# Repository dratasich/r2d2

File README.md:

# r2d2
Software, 3D drawings for R2D2 build.

## Contents

* `firmware_uc_body` contains the sources for the ATmega2560 microcontroller
  (Arduino Mega) controlling body parts (e.g., dome motor).

* `cad` contains FreeCAD projects for R2D2 (e.g., custom dome bearing).

* `pcb` holds Kicad projects for PCBs used in R2D2 (e.g., motor driver shield).

## Dependencies

For some cad drawings the library
[JohK/nutsnbolts](https://github.com/JohK/nutsnbolts) is used.

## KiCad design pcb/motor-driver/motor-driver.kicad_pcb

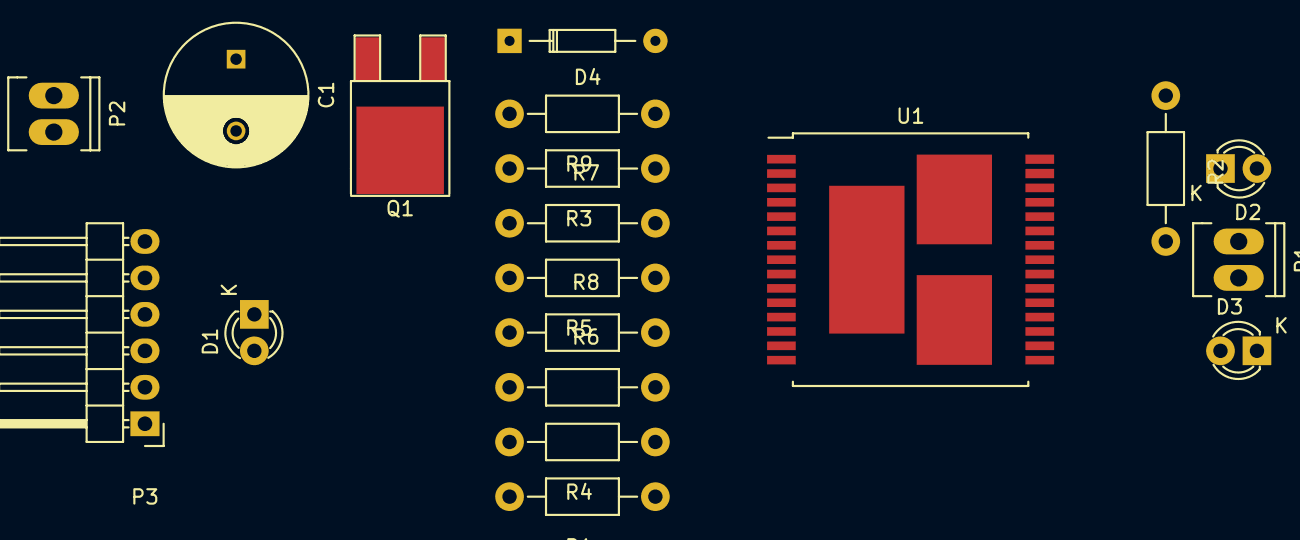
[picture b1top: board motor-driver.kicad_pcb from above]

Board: 2 copper layers, 19 parts (0 on the bottom side), 18 nets, no tracks yet.

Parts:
C1: 1u; C_Radial_D10_L20_P5
D1, D2, D3: LED; LED-3MM
D4: ZENER; Diode_DO-35_SOD27_Horizontal_RM10
P1, P2: CONN_01X02; Socket_MOLEX-KK-RM2-54mm_Lock_2pin_straight
P3: CONN_01X06; Pin_Header_Angled_1x06
Q1: IRF540N; TO-252-2Lead
R1: 330R; Resistor_Horizontal_RM10mm
R2: 120R; Resistor_Horizontal_RM10mm
R3, R4, R5: 1k; Resistor_Horizontal_RM10mm
R6, R7: 3k3; Resistor_Horizontal_RM10mm
R8: 1k5; Resistor_Horizontal_RM10mm
R9: 100k; Resistor_Horizontal_RM10mm
U1: VNH2SP30-E; MultiPowerSO-30_16x17.2mm_Pitch1mm

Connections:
+5V: P3.1, R1.1, R6.1, R7.1
/CS: P3.5, R8.2, U1.9
/INA: P3.3, R3.2
/INB: P3.4, R4.2
/OUTA: P1.1, R2.2, U1.1, U1.25, U1.30
/OUTB: D2.1, D3.2, P1.2, U1.15, U1.16, U1.21
/PWM: P3.2, R5.2
Earth: D1.1, P2.2, P3.6, Q1.3, R8.1
unnamed: C1.2, D4.2, Q1.2, U1.18, U1.19, U1.20, U1.26, U1.27, U1.28
unnamed: D1.2, R1.2
unnamed: D2.2, D3.1, R2.1
unnamed: D4.1, Q1.1, R9.2
unnamed: R3.1, U1.5
unnamed: R4.1, U1.11
unnamed: R5.1, U1.8
unnamed: R6.2, U1.10
unnamed: R7.2, U1.6
VCC: C1.1, P2.1, R9.1, U1.3, U1.13, U1.23

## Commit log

2016-05-14 first test of dome motor
2016-05-16 change dome motor to dc motor
2016-06-05 add dome bearing 3d
2016-10-31 add motor to dome wheel coupling 3d
2016-10-31 renamed folder 3d_models -> cad
2016-11-01 add schematic for motor driver
2016-11-01 rename motor-shield -> motor-driver
2016-11-02 update net list
2016-11-02 add layout (draft)
2016-12-30 add ankle bracelet
2017-01-07 add conversion script (blueprint to custom measures)
2017-02-19 add cad for dome motor
2017-06-01 add ankle cad
2017-06-01 add cad symlink (just to show how it works)
2017-11-07 move firmware
2017-12-27 add code for controlling front logic display
2017-12-28 enable selection of resolution of gptimer
2017-12-28 add code controlling rear logic display
2017-12-31 fix front logic display columns
2018-01-06 fix final rear logic display wiring
2018-01-06 add logic display mode to print char
2018-01-06 add logic display mode chaser
